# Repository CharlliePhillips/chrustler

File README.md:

# The Chrustler
  Chrustler is a combination of the words 'chord' (what the instrument plays) 'Rust' (the language the software is written in) and 'sampler' (the family of instruments it belongs to). This instrument takes in samples recorded using the device or loaded from a USB drive and detects their frequency. Then the user can play that sample as chords in one of the western music scales. The device runs Raspbian Linux and the Rust program in this repo is started automatically by placing the [autostart folder](https://github.com/CharlliePhillips/chrustler/tree/main/autostart) in `~/.config`. This is my final project for CS3651 (Prototyping Intelligent Devices) at Georgia Tech.  [A video demonstration is available on Youtube.](https://youtu.be/KlqjkN_t0CQ)

## Hardware
  1. Brains: Raspbery Pi Zero 2 W  
    - Runs the software itself.
  2. I2S audio card: IQuadIO Codec Zero  
    - Used for internal mic and speaker, AUX in and out headers.  
    - Also has a 5 band EQ used for the high and low pass filters.
  3. Display: SSD1309 I2C (128x64 2.5in OLED)  
    - Displays current playback information.
  4. Time of Flight sensor: ST Micro VL53L1X  
    - Has 2 regions of interest where the right side controls the level of the high frequencies (low pass filter), and the left side controls the level of the low frequencies (high pass filter)
  5. MCP23017 GPIO extender  
    - Provides additional GPIO for keypad input.
  5. PD Trigger Board  
    - Takes USB-C PD and turns it into 5V to power everything.
  6. USB-C “flush” mount extension  
    - This is intended for installation in a car to add a USB-C port, but provides a way to panel mount the power input (and USB-C is better than micro-B on the pi).
  7. 2x 3.5mm TRS female jacks  
    - Connected to the AUX in and out headers on the Codec Zero for external audio IO.
  8. Micro USB OTG cable  
    - Used to expose a full size USB port for portable loading and storing of sample files.
  9. 1W 8ohm 3.6cm speaker  
    - Connected to the Codec Zero as the internal speaker.
  10. Proto-board  
    - Used for a 5V and ground buses as well as I2C data and clock buses.
  11. Custom PCB for 4x4 Cherry-style mechanical key switches  
    - Designed in KiCAD and manufactured at the GT Hive to hold 16 cherry-style switches and the MCP23017. The KiCAD project and board drawings are in [/keypad_pcb/](https://github.com/CharlliePhillips/chrustler/tree/main/keypad_pcb)  
  12. 16x Otemu Lemon switches  
    - Spare linear Cherry-style switches I had that felt nice for the primary input method.  
  13. 2x Addicore AD267 Rotary Encoders (from class kit)  
    - Included in parts kit for class and used for volume adjustment, IO change, key change, and sample selection.  
  14. 1-2 GPIO duplication module  
    - Gives one set of 40 GPIO pins to connect to the Codec Zero, and another for the other GPIO devices, I2C, and power.  
  15. 8x m2.5 screws & heat set inserts
  16. 12x m3 screws & heat set inserts
  17. 3D printed Chassis  
    - Housing with standoffs to add heat-set inserts, and mount everything nicely. Designed in OpenSCAD.
  18. 3D printed faceplate with acrylic window  
    - Covers the main chassis and has inset text to identify IO ports, Encoder functions, and internal microphone location. Designed in OpenSCAD.  
    - The file for the chassis and faceplate is at [scad/chrustler chassis.scad](https://github.com/CharlliePhillips/chrustler/tree/main/scad/crustler%20chassis.scad).  
  19. 2x 3D printed standoffs  
    - used to support the Codec Zero on top of the Pi accounting for the height added by the GPIO duplicator. Designed in OpenSCAD, file is at [scad/soundcard standoff.scad](https://github.com/CharlliePhillips/chrustler/tree/main/scad/soundcard%20standoff.scad)  
  20. 16x 3D printed keycaps  
    - Custom 3D printed keycaps with the appropriate legends built from the [keycap playground OpenSCAD repo](https://github.com/riskable/keycap_playground).  
    - My modified version of the keycap plaground file is at [/scad/keycap_playground/keycap_playground.scad](https://github.com/CharlliePhillips/chrustler/tree/main/scad/keycap_playground/keycap_playground.scad). This was used to make a base stl file, and then imported to [/scad/legend_caps.scad](https://github.com/CharlliePhillips/chrustler/tree/main/scad/legend_caps.scad) to add the legends.
  21. 2x encoder caps  
    - Spares I had from an SP404-OG after replacing them on that device.

## Libraries
  I wanted to write the software in Rust from the start and it provides a nice way to handle interrupts/multithreading, errors, and has pretty good library support on Raspberry Pi devices. I used Rust's standard library, and a couple of other common ones such as `serde` for storing the time of flight sensor's calibration data. The notable libraries used in the program are:
  1. [pitch-detection](https://docs.rs/pitch-detection/latest/pitch_detection/)  
    - Provides a function for detecting the audio frequency on an array of individual sample points from an audio file.
  1. [awedio](https://docs.rs/awedio/latest/awedio/index.html)  
    - This library handles the playback of samples and provides functions to adjust the speed of the sample (very important for pitch correction) as well as a controller to stop/gate the playing samples.  
    - During development I kept running into an integer overflow issue when playing long samples. To fix this I changed a bunch of the related variables from unsigned 32 bit to unsigned 64 bit numbers.  
    - [My fork](https://github.com/CharlliePhillips/awedio64)
  2. [vl53l1x-rs](https://docs.rs/vl53l1x/latest/vl53l1x/)  
    - This library provides functions for the time of flight sensor.  
    - This nor any other 3rd party library I could find supported all five calibration functions, and so I added wrappers to the ST Micro API for them.  
    - Additionally the `usleep()` function in the ST Micro library this crate wraps wasn't compiling on the Pi, so I changed it to `nanosleep()`.  
    - [My fork](https://github.com/CharlliePhillips/vl53l1x-rs)
  3. [rppal](https://docs.rs/rppal/latest/rppal/)  
    - Provides functions to access the GPIO and I2C hardware on the Pi.
  4. [mcp23017](https://docs.rs/mcp23017/latest/mcp23017/)  
    - Provides functions to interface with GPIO on the MCP23017.
  5. [ssd1306](https://docs.rs/ssd1306/latest/ssd1306/)  
    - Provides structures and functions to interface with an SSD1306 display.  
    - The SSD1306 display is identical to the SSD1309 display used for this project (aside from the physical size, and default address), and by changing the I2C address provided during initialization is cross-compatible.
  6. [embedded-graphics](https://docs.rs/embedded-graphics/latest/embedded_graphics/)  
    - Provides structures and functions for creating the text shown on the display.  

  - The libraries' documentation is linked where their git repos can also be found.

  - I also used the [BOSL2](https://github.com/BelfrySCAD/BOSL2) OpenSCAD library for making cubes with rounded corners.

## Learned Skills
  1. Time of Flight Sensor(s)  
    - Before taking on this project I was totally unaware that this type of distance sensor existed. I had originally intended to use an ultrasonic sensor, or a more traditional IR sensor.  
    - I picked the model of ToF sensor I did because of it's existing Rust library support, and the user programmable Regions of interest. Those regions of interest will still pick up on objects outside the region of interest if they cover enough of the sensor's field of view but work reasonably well with two hands at different distances.  
    - It is pretty easy to interface with the sensor over I2C but they do not come calibrated from the factory and must go through a 3-step calibration process in order to get accurate readings that properly distinguish between the regions of interest.  
      1. SPAD - This is calibrated at the factory but without a cover glass that I used on my prototype. It selects the best of the sub-sensors on the device to use.  
      2. Offset - The device being soldered down and added cover class can introduce an offset in distance readings, this measures and corrects for that.  
      3. Cross-talk - The cover glass can cause some of the light emitted to bounce back into the sensor prematurely. This step compensates for that.  
  2. Heat set inserts (talk about borked one)  
    - I was familiar with this process before but had never done it myself. Getting the holes for the inserts correct took some trial and error, and when it came to insert some for testing I found that making a hole bigger with a soldering iron while the insert is half-inserted is a quick way to get plastic stuck in the insert and make it unusable.
  3. Multi-color 3D printing  
    - I had only done single-colored prints before and OpenSCAD has support for color, but it will not export those colors with STL files. In order to add color I created a small indent in the parts that the Bambu slicer would not recognize as a seperate layer, and then used the color painting/fill tool with edge detection to color the text.  
    - I also found that printing the "base" color before the text caused it to come out messy and distorted. When the text is printed before the rest of each layer though, it comes out crisp and very nice looking.  
    - Example of printing the base color before the text:  
      
    - Printing the parts face down (with the text on the bottom layers) also gives the final product a clean, textured finish. See the photos at the end for the final product.
  4. Iterating on CAD designs  
    - The core part of the chassis has a lot of pretty precise measurements to hold everything in place. Instead of re-printing the entire base (10+ hours) each time I had to make an adjustment, I printed skeletons and small sections of the part to make sure everything fit.  
    - Using pins printed where the screws would go later helped hold things in place when test fitting the hardware.  
    - This was also useful for getting the sizing of the keycaps correct given that I'm using a non-standard plate.  
    - The following photos go left to right, top to bottom for first iterations to most recent:  
      - Main Chassis Skeleton:  

      - IO Panel:  

      - USB panel and restraint:  

      - Keycaps:  

 <div style="page-break-after: always;"></div>
  
  5. Linux audio  
    - I've used Linux for quite some time to do multimedia work (always requires some fidling), but I haven't had to get in the weeds quite like this before.  
    - The volume, filter and adjustments along with the IO toggle both use `amixer` commands issued by the Rust program to change the relevant settings. This was easy to test using the `alsamixer` TUI and then translate into commands using the indices given by `amixer -c -1 controls`.  
    - I used `arecord` commands issued by the Rust program to do the audio recording as the simplest Rust interfaces for this were overcomplicated for my use case. When testing recording and playback in the final program I ran into a weird issue with lots of noise in the recordings from the program that didn't exist using the commands by themselves. After some troubleshooting I discovered that the audio device was opened in 32 bit PCM mode by the `awedio` library but I was recording in 16 bit mode as that is the actual format used by the library. Switching the recordings to 32 bit mode fixed this issue.
  6. PCB Fabrication  
    - To have a "macro" pad with Cherry-style switches that fit in the small size I wanted for the enclosure I had to design my own.  
    - Picking up KiCAD to recreate the simple circuit from the membrane pad given in our class kits was fairly easy, and a lot of resources exist online from the custom keyboards community to quickly get a model running. There was also a fellow student familiar with the process who was able to give me some design tips to make sure that my first run of the board would work, and be my last.  
    - The Hive makerspace at school had excellent documentation on using their PCB fabrication equipment (LPKF ProtoMat S103, and ProtoLaser U4). From there it was fairly easy to get everything going, and once finished then I was able to solder the switches and MCP23017 using my own equipment.  
    - The underside of the keypad PCB (the top side is just plain copper):  

 <div style="page-break-after: always;"></div>

  7. Acrylic Crazing and I2C Speed/Capacitance Relationship  
    - These two weren't part of skill demos for the class but my instructor Scott taught me about these when I was curious about some of these finer details.  
    - Securing acrylic with the right adhesive is important, as many adhesives will cause stress on top of that introduced by laser cutting. This additional stress can cause micro-cracks called "crazing" and is caused by adhesives with solvents like alcohol. To demo this he sprayed some dry erase fluid on an some laser cut acrylic scrap, and cracks started to form in less than a minute.  
    - I had some extra JB weld and thought that might work well so I used it on another piece of acrylic scrap and attached it to the first chassis skeleton (but it broke during stress testing):  
      
    - I was worried about cramming too much near the I2C bus circuitry and causing interference. I2C operates at a constant clock but the data experiences some curve in the rise time of the signals. Scott explained how this curve is dictated by the capacitance of the wires which ensured me that I didn't have to be too careful about where to place these signal wires inside of the enclosure.  
  
<div style="page-break-after: always;"></div>

## Iteration Process
### Initial Testing
  1. Proof of Concept Program.  
    - My first work on this project was a simple program that recorded a sample, then corrected the pitch it and played back as a C-Major triad.  
    - Once I had acquired some of the hardware for the prototype I added the time of flight sensor readings to adjust a filter on this chord as it looped indefinitely.  
    - [Repo for this test](https://github.com/CharlliePhillips/crustler_poc)
  2. GPIO Test Program   
    - I also created a separate test program to hook up the remainder of the input hardware to to figure out a good setup for reading everything but the TOF sensor.  
    - [Repo for this test](https://github.com/CharlliePhillips/chrustler_btn_test)
  3. Testing Breadboard  
    - For these test programs and much of the development of the main program I had all of the hardware connected to a breadboard. This made it easy to disconnect things to take measurements for the chassis while still working on the main program, and experiment minimizing the wires needed to connect everything.  
    - Having everything on the breadboard made it easy to hook up parts to the chassis skeleton(s):

<div style="page-break-after: always;"></div>

### Ideas That Didn't Work Out
  1. Battery Power  
    - I had initially planned to add battery power to the device for portability. As I worked on the physical design and test fit the rest of the hardware I realized that there would not be a whole lot of room for the battery, and given the time constraint on the project decided that it could do without and USB-C PD would suffice.  
  2. Filter frequency sweeping  
    - I originally wanted to have the TOF sensor control both the frequency and intensity of the filters with a multi-zone sensor where the frequency would be set by the zone(s) and intensity controlled by the distance, but with poor documentation and 3rd party library support this was out of reach.  
    - When moving to a ROI sensor instead of multi-region one I had instead wanted a fixed intensity where the distance controlled the frequency, but I then found that the audio card I had decided on has a built in 5 band EQ, but it is not parametric.  
    - I finally landed on the distance controlling the intensity of the lower two and upper two frequency bands provided by the built in EQ. The intensity of the "inner" band of each side is halved from the intensity set to the highest and lowest end of the EQ, and this works fairly well as a high, low, or band pass filter.

### Hardware That Had To Be Changed
  1. Keypad
    - As alluded to before I originally was using a 4x4 membrane keypad as the primary input for the device. This really sucked,  it was hard to tell when I was pressing the button or not, and it was very small making it a little hard to play multiple chords in succession.
    - This shows how small the original pad was compared to the one I made:  
    
    - Creating my own keypad fixed these problems, and also let me change the legends on the keys for a more intuitive arrangement of the inputs.  
  2. SD Card – OTG adapter
    - My original idea for loading external sound files was to use an SD card like on devices like the SP404 MKII and modern (or modernized) MPC devices. This is sort of what the format is intended for, but requires an SPI connection from the limited GPIO I had after adding the sound card.  
    - To simplify things I decided to mount a micro-B OTG adapter inside of the device that connects directly to the Raspberry Pi. This let me focus on getting the file navigation part of my code working correctly and should theoretically not be too difficult if I were to add it in the future.  

### Lessons Learned
  1. Calibrate Your ToF Sensor    
    - Before calibration the ToF sensor readings where all over the place. Adding the Rust calibration functions to the library I used and sitting through the calibration process was something I should have considered from the start and was absolutely worth it.
  2. Consider cable management  
    - Despite not needing to be too worried about I2C interference I should have spent some more time considering where to route all of the wires inside of the device. It is a bit of a rats nest, and with a little more thought, I think I could do much better.  
  3. Test Physical Design With Small Parts   
    - The 3D print iterations shown above were key to getting my physical design just right.  
    - I hadn't taken on a 3D modeling and design project of this scale before, and had never needed to do more than a couple of full prints to get something the way I wanted. I was still pretty uncertain about my measurements at each stage and printing only the parts I was concerned about saved me a lot of time and filament.  
  4. ALSA(mixer) is fun  
    - Using the ALSA programs that come with Raspbian Linux (and most desktop Linux distros) made a lot of things I was uncertain about programming much easier than anticipated.  
    - If I ever do other audio-intense programming projects I will be considering some of these same techniques to make my life easier. I know this is sorta the "Unix Philosophy" but often times built in programs don't come with quite everything I want them to, and this was not the case here.  

  #### Other Potential Improvements
  1. More thorough recording (i.e. adjustable count in, timed recording, input level)  
    - Other sampler instruments offer these sorts of things, and they could be useful here as well.
  2. Simple sample trimming  
    - This would mean you don't have to start playing your recording as soon as or before the recording starts, and would be a very nice qol feature.
  3. Analog Chord Keys  
    - Using optical or hall-effect analog mechanical keyboard switches could be a nice way to keep the same form factor while adding velocity to the input. This would require a more complex PCB though and those switches are much harder to come by.
  4. Stereo sound  
    - All of the sound on this device is mono, and the audio IO is all wired as mono. This was to reduce possibilities while programming and still sounds great (especially for a prototype), but stereo is the standard and would improve the quality of the sound produced.  

<div style="page-break-after: always;"></div>

## The Final Prototype
A photo taken during assembly:

<div style="page-break-after: always;"></div>

Overview of the final prototype:

<div style="page-break-after: always;"></div>

Main IO panel on the final prototype:

USB Panel on the prototype:

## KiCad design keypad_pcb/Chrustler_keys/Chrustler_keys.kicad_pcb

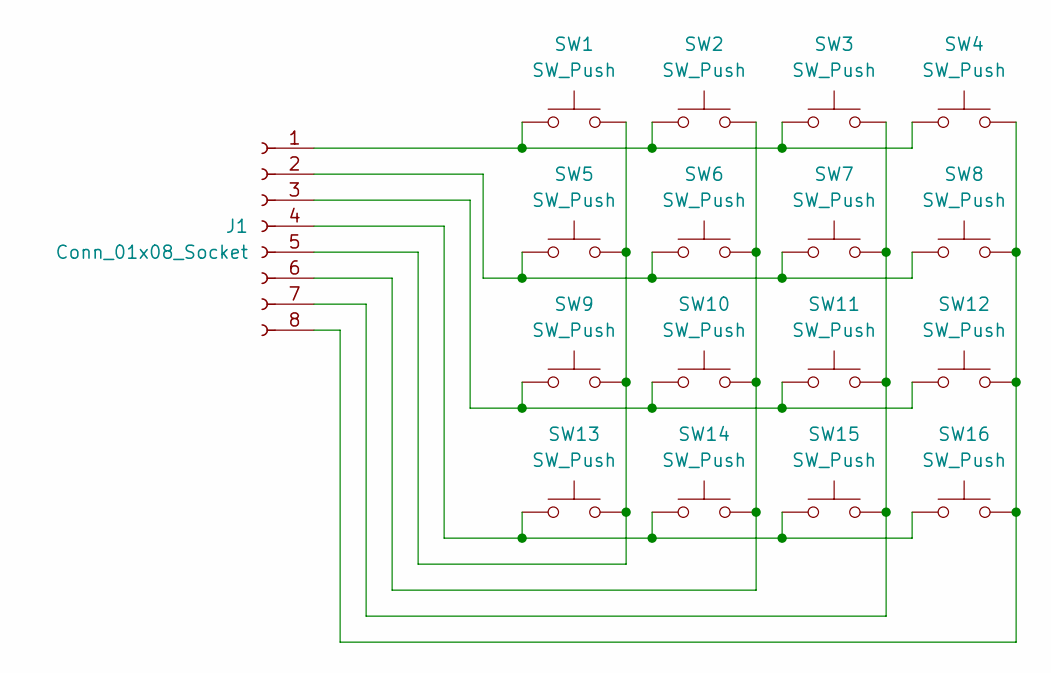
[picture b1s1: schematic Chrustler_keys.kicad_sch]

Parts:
J1: Conn_01x08_Socket; PinSocket_1x08_P2.54mm_Vertical
SW1, SW2, SW3, SW4, SW5, SW6, SW7, SW8, SW9, SW10, SW11, SW12, SW13, SW14, SW15, SW16: SW_Push; SW_Cherry_MX_1.00u_PCB

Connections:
unnamed: J1.1, SW1.1, SW2.1, SW3.1, SW4.1
unnamed: J1.2, SW5.1, SW6.1, SW7.1, SW8.1
unnamed: J1.3, SW9.1, SW10.1, SW11.1, SW12.1
unnamed: J1.4, SW13.1, SW14.1, SW15.1, SW16.1
unnamed: J1.5, SW1.2, SW5.2, SW9.2, SW13.2
unnamed: J1.6, SW2.2, SW6.2, SW10.2, SW14.2
unnamed: J1.7, SW3.2, SW7.2, SW11.2, SW15.2
unnamed: J1.8, SW4.2, SW8.2, SW12.2, SW16.2

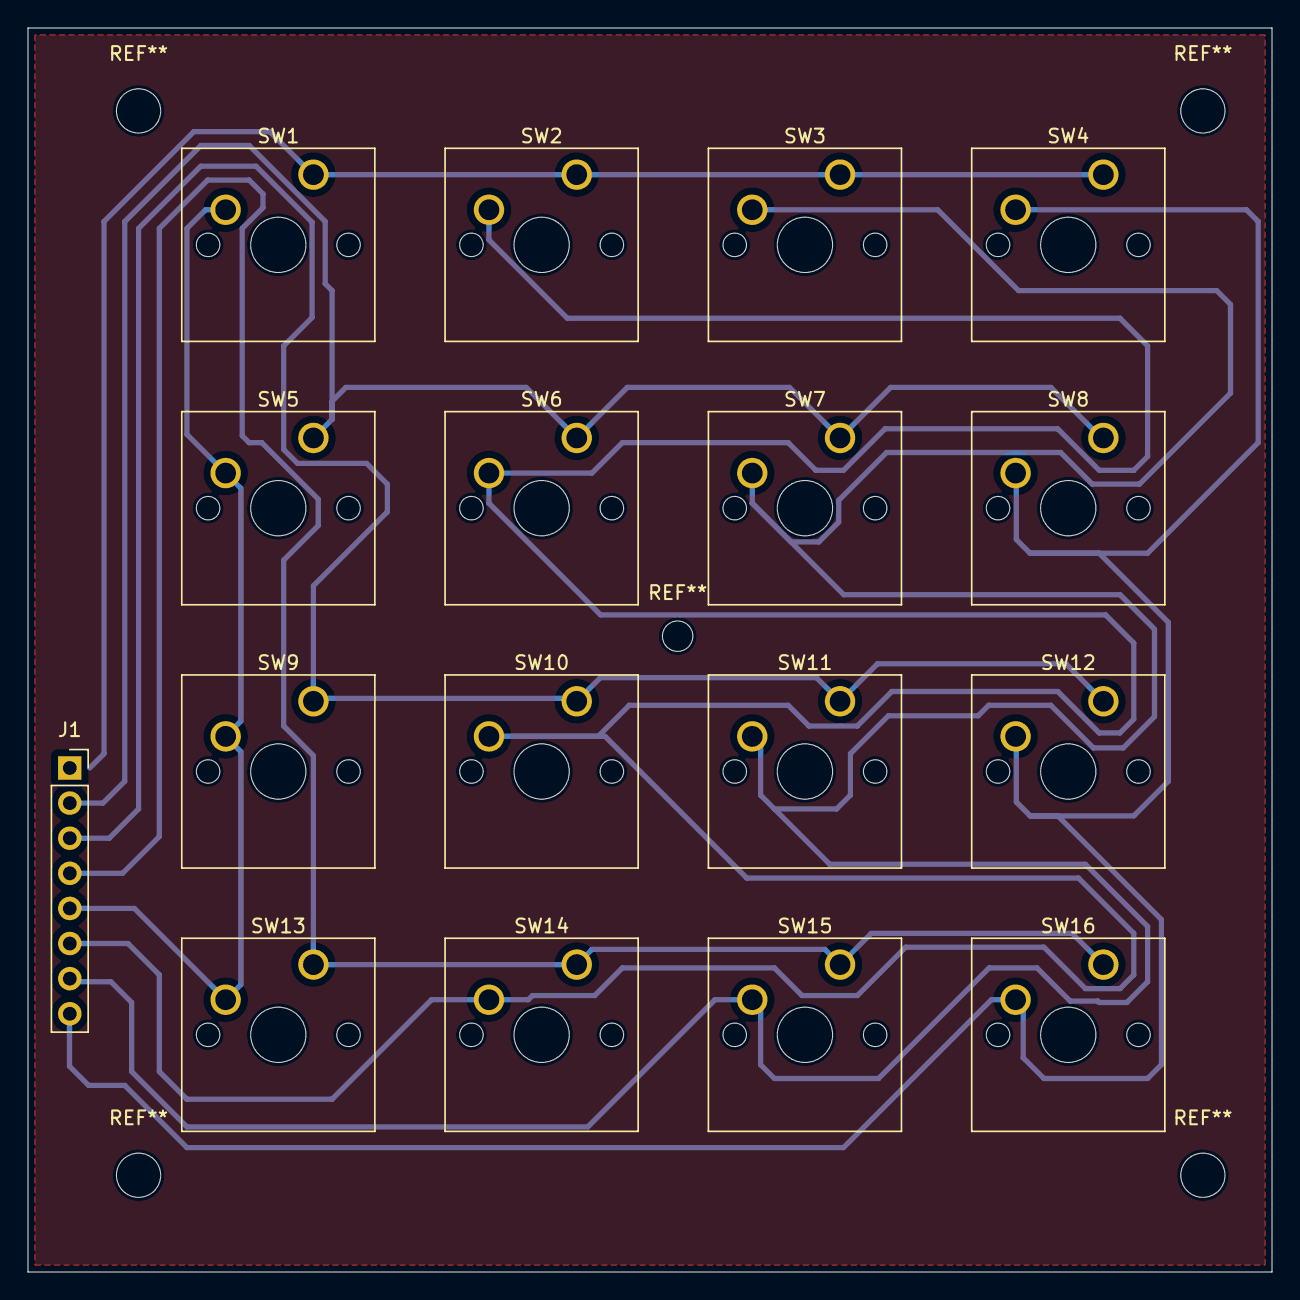
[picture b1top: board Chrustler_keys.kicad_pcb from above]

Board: 2 copper layers, 90.0 x 90.0 mm, 17 parts (0 on the bottom side), 8 nets.

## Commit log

2025-11-10 init commit for final program
2025-11-10 change display address
2025-11-11 kinda works
2025-11-11 test input
2025-11-11 add some display
2025-11-11 tune display
2025-11-11 a few little tweaks
2025-11-11 fix octave shifting
2025-11-11 fix filter strength
2025-11-11 fix hi octave display
2025-11-12 tof debug print
2025-11-12 tof fix?
2025-11-12 eq fix
2025-11-12 add filter level display
2025-11-12 remove tof print
2025-11-12 fix sound overlap
2025-11-12 incorrect note indecies
2025-11-12 tweaks
2025-11-12 test tweaks
2025-11-12 that didn't work
2025-11-12 fix maj/minor cache flush
2025-11-12 add root note playback
2025-11-12 add volume and key change
2025-11-12 fix? key change and volume display
2025-11-13 adjust volume with LUT
2025-11-13 correct volume display
2025-11-13 add file select
2025-11-13 oops
2025-11-13 fix up a couple things
2025-11-13 hopefully one last mistake for file selection fixed
2025-11-13 this actually do it?
2025-11-13 sample select rollover fix?
2025-11-13 forgot about gating for sample select
2025-11-13 add recording, outline audio IO change
2025-11-13 fix filename parsing + delay after error screen
2025-11-13 fix filename parsing
2025-11-13 why so loud?
2025-11-13 I swear if this is why
2025-11-13 I hope this works...
2025-11-13 debugging cpal now
2025-11-14 try fixing buffer size
2025-11-14 that's a weird one
2025-11-14 uncomment and remove debugging code
2025-11-17 add internal/external io switching
2025-11-17 fix ghost USB possibility and update TOF ROIs
2025-11-17 alsa is really wierd about that
2025-11-17 minor mistake
2025-11-17 fix root note playback
2025-11-17 tweak input time
2025-11-17 adjust alsa values
2025-11-18 add calibration functionality
2025-11-19 bruh
2025-11-19 more little fixes
2025-11-19 hope this works
2025-11-19 this should work...
2025-11-19 my bad
2025-11-19 ok that was way longer than i expected
2025-11-19 expect strange behavior
2025-11-19 i'm too tired to be coding rn
2025-11-19 works, adjust cutoff distance again
2025-11-19 remove unneeded comments
2025-11-20 add L/R TOF cyle, and modify key map
2025-11-20 add a couple of missed tof updates
2025-11-20 start README/writeup
2025-11-20 I messed up the filter function again
2025-11-20 fix TOF:HF/LF display
2025-11-20 add more scad files, and keypad PCB
2025-11-20 update autostart script
2025-11-24 adjust TOF and continue work on writeup
2025-11-24 writeup looking good
2025-11-24 make image paths relative
2025-11-25 revise writeup, just need demo video
2025-11-26 add demo video link
2025-11-26 github wierd about bullets
